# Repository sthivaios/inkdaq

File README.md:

# InkDAQ

## Introduction

InkDAQ is a system that acquires telemetry data from a pen, in order to assess one's handwritig.

At the moment, the project is in very early stages, and will only measure the writing force. Sensors to measure data such as grip force, or an accelerometer (to measure one's writing speed) might be added in the future.

It is designed to be a modular system, with a custom-designed external data acquisition device, while the pen will act as a passive sensor probe, connected via a cable to the DAQ device, to allow for a more modular approach as the pen can be changed.

## Contributing

You are welcome to contribute to the project by creating issues if you find any bugs or want to request a new feature. However, due to the project's extremely early stage, please avoid pull requests for now.

If you are contributing to the project, make sure you understand the license terms of the part that you are contributing to. Read LICENSE for more information.

## Licensing

This project contains multiple components under different licenses. See [LICENSE](LICENSE) for more details.

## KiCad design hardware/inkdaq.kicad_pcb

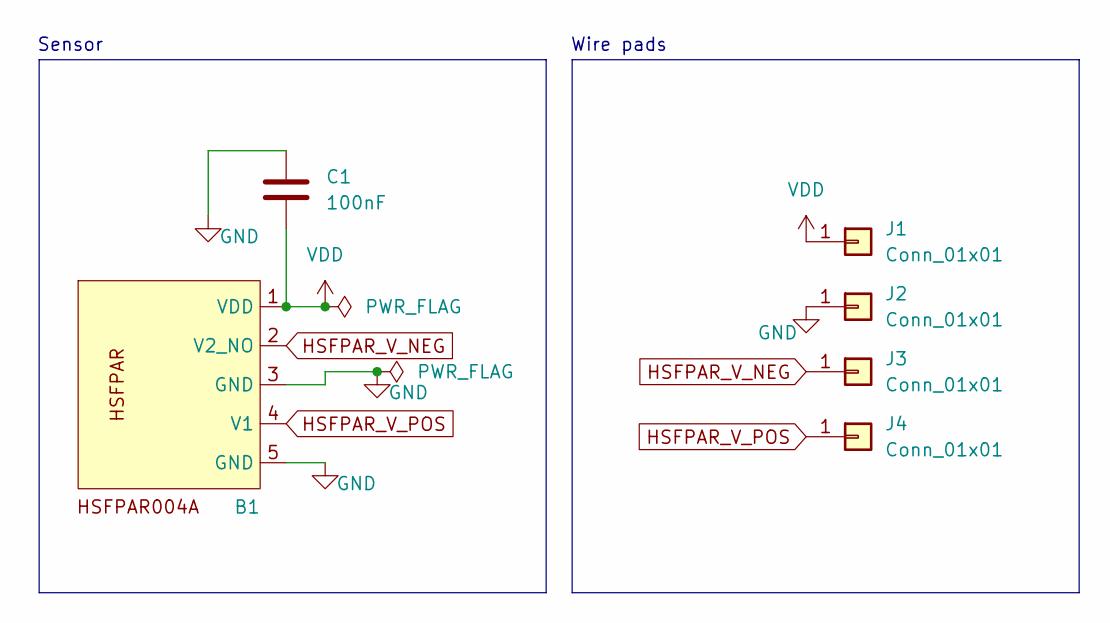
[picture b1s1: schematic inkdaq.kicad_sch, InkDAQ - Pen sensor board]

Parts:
B1: HSFPAR004A; LCSC C470800
C1: 100nF; C_0201_0603Metric; LCSC C22435929
J1, J2, J3, J4: Conn_01x01; WirePad_1mm_Square

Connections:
GND: B1.3 (GND), B1.5 (GND), C1.1, J2.1
HSFPAR_V_NEG: B1.2 (V2_NO), J3.1
HSFPAR_V_POS: B1.4 (V1), J4.1
VDD: B1.1 (VDD), C1.2, J1.1

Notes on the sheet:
Sensor
Wire pads

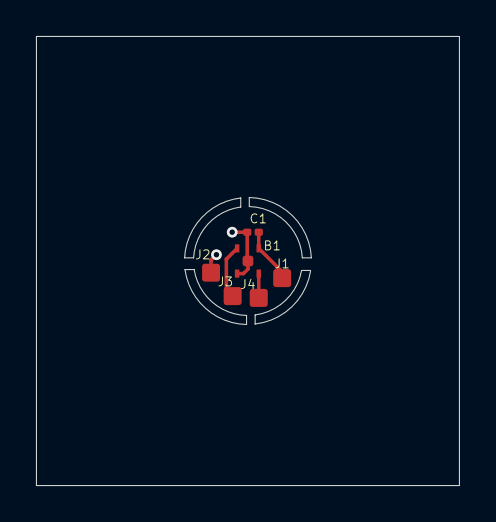
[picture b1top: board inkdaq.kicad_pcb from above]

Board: 2 copper layers, 23.5 x 25.0 mm, 6 parts (0 on the bottom side), 4 nets.

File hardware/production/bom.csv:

Designator,Footprint,Quantity,Value,LCSC Part #
B1,HSFPAR004A,1,~,C470800
C1,0201,1,100nF,C22435929
"J1, J2, J3, J4",WirePad_1mm_Square,4,Conn_01x01,

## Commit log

2026-03-01 init
2026-03-01 add hardware/LICENSE
2026-03-01 create kicad project
2026-03-01 create HSFPAR004A symbol and footprint
2026-03-01 create very rough FPC
2026-03-01 add LCSC part numbers
2026-03-01 generate 1.0 prod files
2026-03-01 my awful attempt at making a breakaway pcb in a larger panel since JLC doesnt like it being so small
2026-03-01 generate 1.1 prod files
2026-03-02 remove INA333 from schematic; add wire pads
2026-03-02 set footprint for HSFPAR's decoupling cap C1
2026-03-02 create 1mm square smd wire pad; use it in schematic for wires
2026-03-02 route pcb
2026-03-02 make pcb 3mm radius and not 6mm (i thought it was the diameter lol)
2026-03-07 generate 2.0 prod files
2026-03-07 pcb: panelize in order to be able to use JLCPCBA
2026-03-07 generate 2.1 prod files
2026-03-07 pcb: larger panel, generate v2.2 gerbers
2026-03-07 pcb: more modifications to the panel, generate v2.3 gerber files
2026-03-08 pcb: i dont even know what changed but i'll commit anyway

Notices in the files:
hardware/inkdaq.kicad_pcb:
CERN Open Hardware License v2 - Strongly Reciprocal
Copyright © 2026 Stratos Thivaios
